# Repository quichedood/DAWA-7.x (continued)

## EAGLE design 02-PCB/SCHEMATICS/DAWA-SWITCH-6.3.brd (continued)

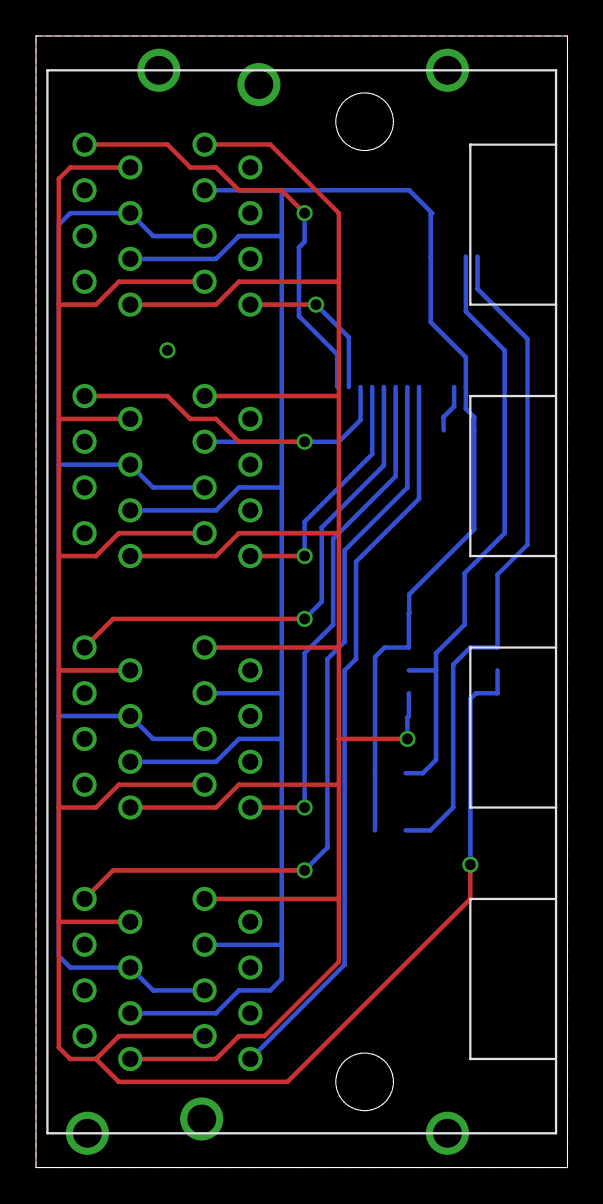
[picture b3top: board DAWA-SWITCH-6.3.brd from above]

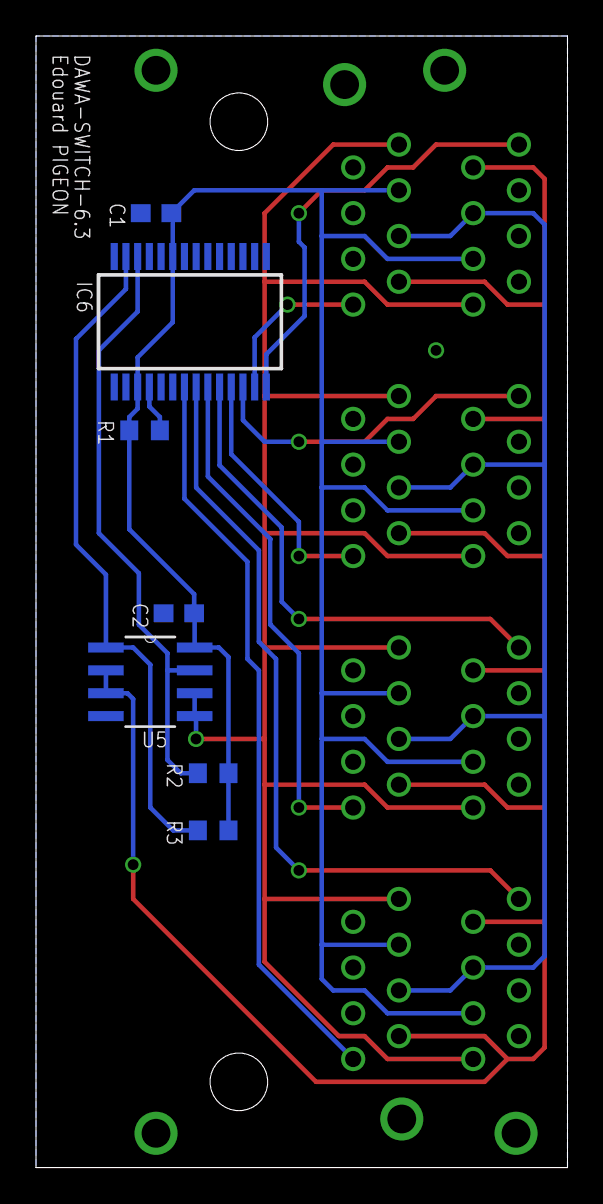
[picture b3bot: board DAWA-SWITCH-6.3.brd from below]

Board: 2 copper layers, 29.5 x 62.9 mm, 8 parts (7 on the bottom side), 16 nets.

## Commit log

2021-05-20 :circus_tent: Added .gitattributes & .gitignore files
2021-05-20 First commit
    Work in progress
2021-10-10 New revision
2021-10-10 Ublox NEO-M8Q
2021-10-31 multiple updates
    multiple updates
2023-03-04 Libs major update
    Use BusIO from Adafruit, test and update all libs to latest versions.
2023-03-05 Documentation TFT
